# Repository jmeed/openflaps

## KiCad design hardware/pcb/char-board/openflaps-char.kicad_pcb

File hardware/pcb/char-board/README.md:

# Character Board (v0.1 draft)

One board per character, a drop-in replacement for the dowjames v5.1 module board in
[DrewFerg11/Split-Flap-Display](https://github.com/DrewFerg11/Split-Flap-Display). It
keeps Drew's outline and puts PREV, NEXT, MOTOR and HALL exactly where his board has
them (copied from his Edge_Cuts gerber and drill file), so it sits in his enclosure and
plugs into its neighbours the same way. It replaces I2C with the OpenFlaps UART ring:
no DIP switches, no address limit, addresses come from position in the chain.

Status: schematic drafted, outline and placement done, **not routed, not ERC/DRC
checked**. Not ordered.

| File | What |
|---|---|
| `gen_schematic.py` | Generates the schematic and symbol library |
| `gen_pcb.py` | Generates the board: Drew's outline, footprints placed, pads netted, no tracks |
| `openflaps-char.kicad_sch` / `.kicad_pcb` / `.kicad_pro` | KiCad project (opens in KiCad 7 or newer) |
| `Schematic_Character_Board.pdf`, `placement.png` | Renders |

Rebuild:

```bash
python3 gen_schematic.py
kicad-cli sch export pdf -o Schematic_Character_Board.pdf openflaps-char.kicad_sch
kicad-cli sch export netlist --format kicadxml -o openflaps-char.xml openflaps-char.kicad_sch
python3 gen_pcb.py   # needs KiCad's pcbnew Python module
```

Once routing starts by hand in KiCad, the `.kicad_pcb` becomes the source of truth and
`gen_pcb.py` should not be re-run over it.

## Circuit

- **MCU** PY32F002AF15P6 (TSSOP-20, LCSC C5292059) at 3.3 V from an XC6206P332MR LDO.
- **Motor**: ULN2003A, inputs PA6, PA5, PF0, PF1, outputs to a horizontal JST XH 5-pin
  (S5B-XH-A, C263757, as Drew), pin 5 = +5 V (red wire). COM to +5 V.
- **Hall sensor** (homing): JST PH 3-pin (C2320, as Drew), pinout `OUT GND +5V` in Drew's
  order so his A3144/WSH130 leads plug in. The sensor runs on 5 V; its open-collector
  output is pulled up to 3.3 V with 10k, so the MCU never sees 5 V. Active low on PB0,
  100 nF filter.
- **Ring link**: Drew's right-angle 1x4 PREV header (C32713263) and NEXT socket
  (C2897386), same positions and same pins 1-2 (GND, +5V). Pins 3-4 change from I2C to
  DATA and RETURN. Data enters at PREV (PA3, USART1 RX via 100 ohm) and leaves at NEXT
  (PA2, TX via 100 ohm). RETURN is a straight trace. Bridge **JP1** on the last board of a
  row to loop DATA back on RETURN.
- **Debug light**: one WS2812B-2020-V6 on 5 V, data from PA7 via 33 ohm (SPI1 MOSI if
  the AF table allows, otherwise bit-banged: one LED is about 30 us). Dim green power LED.
- **Flashing**: SWDIO, SWCLK, NRST, BOOT0, 3.3 V and GND on 1.5 mm pogo pads on the
  bottom, in a 2.54 mm row. BOOT0 has a 10k pull-down.
- **Spare I/O** on 1 mm bottom pads: PA0, PA1, PA4, PB1, PB2, PB3.

## MCU pin map

| Pin | Port | Net |
|---|---|---|
| 6, 7, 8, 9 | PA6, PA5, PF0, PF1 | Motor coils 1-4 (PF0/PF1 free because the internal oscillator is used) |
| 17 | PB0 | Hall sensor, active low |
| 14, 13 | PA3, PA2 | USART1 RX, TX (AF1) |
| 16 | PA7 | WS2812 data |
| 2, 3, 10, 5 | PA13, PA14, PF2, PF4 | SWDIO, SWCLK, NRST, BOOT0 |
| 11, 12, 15, 19, 18, 4 | PA0, PA1, PA4, PB1, PB2, PB3 | Spare pads |
| 20, 1 | VCC, VSS | 3.3 V, GND |

## Not yet checked

- Routing, then ERC and DRC in KiCad 8 or 9.
- PA7 as SPI1 MOSI on the PY32F002A (AF table); PA2/PA3 as USART1 AF1.
- Drew's board has no mounting holes; this one copies that. Check how it is held in the
  enclosure (and the narrower dual-display enclosure from MakerWorld) on a real build.
- LCSC numbers still to pick: 22 uF 1206 bulk cap, 3.3k, 33 ohm, green 0603 LED.
- One power pin per side on the 4-pin link: fine for one motor per board (Drew does the
  same), but inject 5 V every few modules on a long row.

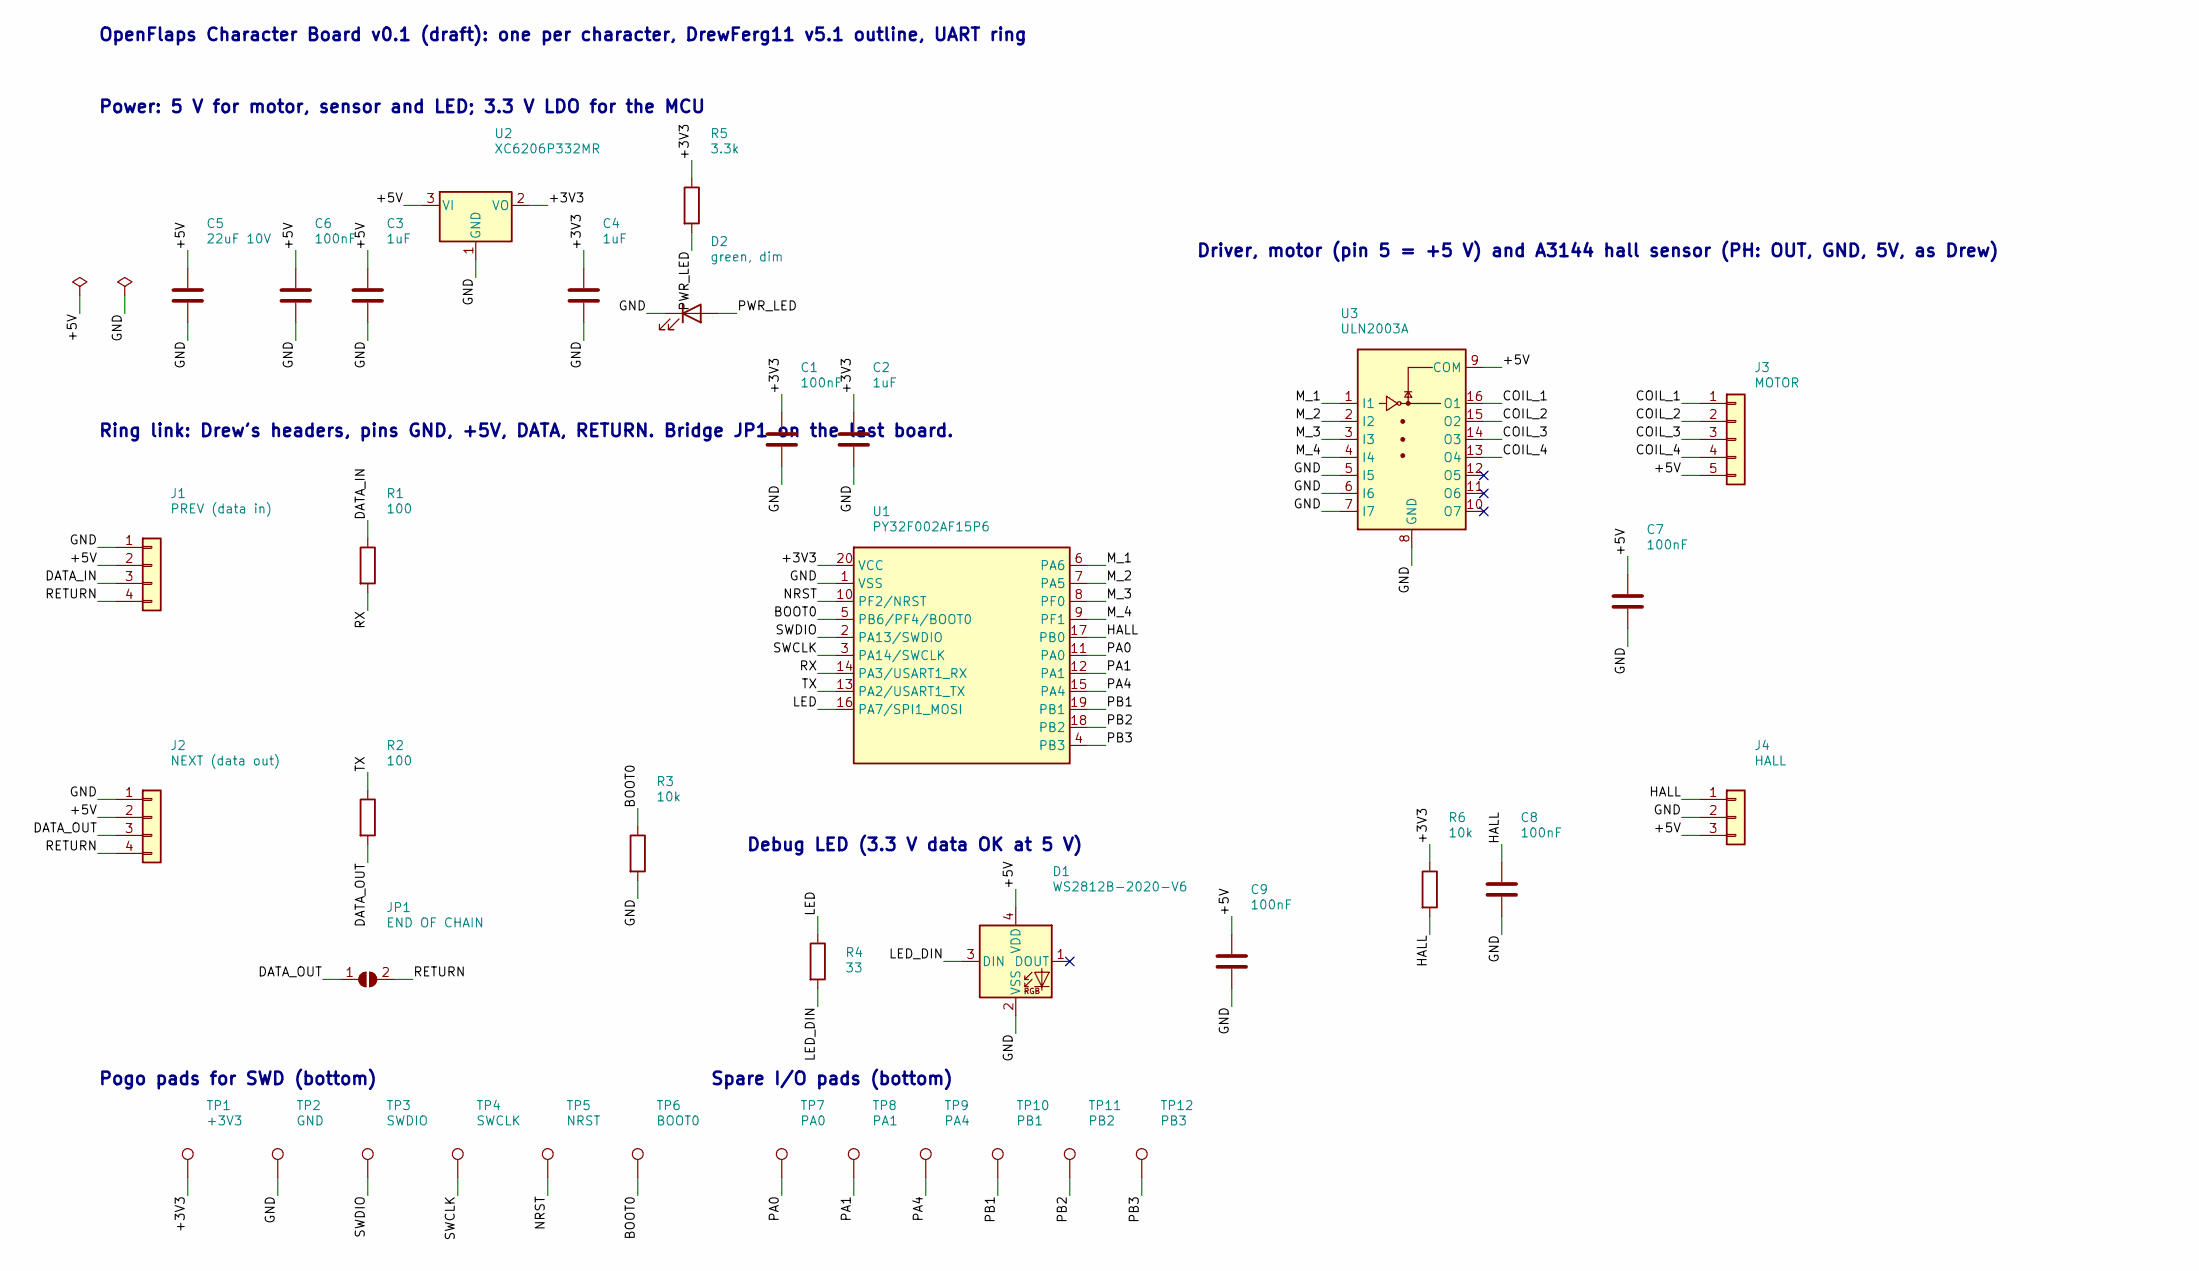
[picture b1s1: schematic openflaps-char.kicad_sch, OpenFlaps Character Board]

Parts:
C1, C6, C7, C8, C9: 100nF; C_0603_1608Metric; LCSC C14663
C2, C3, C4: 1uF; C_0603_1608Metric; LCSC C15849
C5: 22uF 10V; C_1206_3216Metric
D1: WS2812B-2020-V6; LED_WS2812B-2020_PLCC4_2.0x2.0mm; LCSC C52917434
D2: green, dim; LED_0603_1608Metric
J1: PREV (data in); PinHeader_1x04_P2.54mm_Horizontal; LCSC C32713263
J2: NEXT (data out); PinSocket_1x04_P2.54mm_Horizontal; LCSC C2897386
J3: MOTOR; JST_XH_S5B-XH-A_1x05_P2.50mm_Horizontal; LCSC C263757
J4: HALL; JST_PH_B3B-PH-K_1x03_P2.00mm_Vertical; LCSC C2320
JP1: END OF CHAIN; SolderJumper-2_P1.3mm_Open_RoundedPad1.0x1.5mm
R1, R2: 100; R_0603_1608Metric; LCSC C22775
R3, R6: 10k; R_0603_1608Metric; LCSC C25804
R4: 33; R_0603_1608Metric
R5: 3.3k; R_0603_1608Metric
TP1: +3V3; TestPoint_Pad_D1.5mm
TP2: GND; TestPoint_Pad_D1.5mm
TP3: SWDIO; TestPoint_Pad_D1.5mm
TP4: SWCLK; TestPoint_Pad_D1.5mm
TP5: NRST; TestPoint_Pad_D1.5mm
TP6: BOOT0; TestPoint_Pad_D1.5mm
TP7: PA0; TestPoint_Pad_D1.0mm
TP8: PA1; TestPoint_Pad_D1.0mm
TP9: PA4; TestPoint_Pad_D1.0mm
TP10: PB1; TestPoint_Pad_D1.0mm
TP11: PB2; TestPoint_Pad_D1.0mm
TP12: PB3; TestPoint_Pad_D1.0mm
U1: PY32F002AF15P6; TSSOP-20_4.4x6.5mm_P0.65mm; LCSC C5292059
U2: XC6206P332MR; SOT-23; LCSC C5446
U3: ULN2003A; SOIC-16_3.9x9.9mm_P1.27mm; LCSC C5252903

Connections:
+3V3: C1.1, C2.1, C4.1, R5.1, R6.1, TP1.1, U1.20 (VCC), U2.2 (VO)
+5V: C3.1, C5.1, C6.1, C7.1, C9.1, D1.4 (VDD), J1.2, J2.2, J3.5, J4.3, U2.3 (VI), U3.9 (COM)
BOOT0: R3.1, TP6.1, U1.5 (PB6/PF4/BOOT0)
COIL_1: J3.1, U3.16 (O1)
COIL_2: J3.2, U3.15 (O2)
COIL_3: J3.3, U3.14 (O3)
COIL_4: J3.4, U3.13 (O4)
DATA_IN: J1.3, R1.1
DATA_OUT: J2.3, JP1.1 (A), R2.2
GND: C1.2, C2.2, C3.2, C4.2, C5.2, C6.2, C7.2, C8.2, C9.2, D1.2 (VSS), D2.1 (K), J1.1, J2.1, J4.2, R3.2, TP2.1, U1.1 (VSS), U2.1 (GND), U3.5 (I5), U3.6 (I6), U3.7 (I7), U3.8 (GND)
HALL: C8.1, J4.1, R6.2, U1.17 (PB0)
LED: R4.1, U1.16 (PA7/SPI1_MOSI)
LED_DIN: D1.3 (DIN), R4.2
M_1: U1.6 (PA6), U3.1 (I1)
M_2: U1.7 (PA5), U3.2 (I2)
M_3: U1.8 (PF0), U3.3 (I3)
M_4: U1.9 (PF1), U3.4 (I4)
NRST: TP5.1, U1.10 (PF2/NRST)
PA0: TP7.1, U1.11 (PA0)
PA1: TP8.1, U1.12 (PA1)
PA4: TP9.1, U1.15 (PA4)
PB1: TP10.1, U1.19 (PB1)
PB2: TP11.1, U1.18 (PB2)
PB3: TP12.1, U1.4 (PB3)
PWR_LED: D2.2 (A), R5.2
RETURN: J1.4, J2.4, JP1.2 (B)
RX: R1.2, U1.14 (PA3/USART1_RX)
SWCLK: TP4.1, U1.3 (PA14/SWCLK)
SWDIO: TP3.1, U1.2 (PA13/SWDIO)
TX: R2.1, U1.13 (PA2/USART1_TX)

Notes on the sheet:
OpenFlaps Character Board v0.1 (draft): one per character, DrewFerg11 v5.1 outline, UART ring
Power: 5 V for motor, sensor and LED; 3.3 V LDO for the MCU
Ring link: Drew's headers, pins GND, +5V, DATA, RETURN. Bridge JP1 on the last board.
Driver, motor (pin 5 = +5 V) and A3144 hall sensor (PH: OUT, GND, 5V, as Drew)
Debug LED (3.3 V data OK at 5 V)
Pogo pads for SWD (bottom)
Spare I/O pads (bottom)

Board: 2 copper layers, 37 parts (12 on the bottom side), 30 nets, no tracks yet.

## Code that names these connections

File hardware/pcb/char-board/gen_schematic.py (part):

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MCU_LEFT = [  # (number, name, type)
    ("20", "VCC", "power_in"),
    ("1", "VSS", "power_in"),
    ("10", "PF2/NRST", "bidirectional"),
    ("5", "PB6/PF4/BOOT0", "input"),
    ("2", "PA13/SWDIO", "bidirectional"),
    ("3", "PA14/SWCLK", "bidirectional"),
    ("14", "PA3/USART1_RX", "bidirectional"),
    ("13", "PA2/USART1_TX", "bidirectional"),
    ("16", "PA7/SPI1_MOSI", "bidirectional"),
]
MCU_RIGHT = [(n, nm, "bidirectional") for n, nm in [
    ("6", "PA6"), ("7", "PA5"), ("8", "PF0"), ("9", "PF1"),
    ("17", "PB0"), ("11", "PA0"), ("12", "PA1"), ("15", "PA4"),
    ("19", "PB1"), ("18", "PB2"), ("4", "PB3"),
]]


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
# Drew's v5.1 board: PREV is a right-angle 1x4 pin header, NEXT a right-angle 1x4
# socket, both pinned GND, +5V, bus, bus. We keep his pinout and positions and
# turn the two bus pins into DATA and RETURN. Data enters at PREV.
mcu_nets = {
    "20": "+3V3", "1": "GND",
    "10": "NRST", "5": "BOOT0", "2": "SWDIO", "3": "SWCLK",
    "14": "RX", "13": "TX", "16": "LED",
    "6": "M_1", "7": "M_2", "8": "M_3", "9": "M_4",
    "17": "HALL",
    "11": "PA0", "12": "PA1", "15": "PA4", "19": "PB1", "18": "PB2", "4": "PB3",
}
part("U1", "openflaps:PY32F002A", "PY32F002AF15P6", "Package_SO:TSSOP-20_4.4x6.5mm_P0.65mm",
     "C5292059", (139.7, 106.68), mcu_nets, ref_at=(-12.7, -20.32))
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for k, net in enumerate(["+3V3", "GND", "SWDIO", "SWCLK", "NRST", "BOOT0"]):
    part(f"TP{k + 1}", "Connector:TestPoint", net, "TestPoint:TestPoint_Pad_D1.5mm", "",
         (30.48 + k * 12.7, 180.34), {"1": net})
for k, net in enumerate(["PA0", "PA1", "PA4", "PB1", "PB2", "PB3"]):
    part(f"TP{k + 7}", "Connector:TestPoint", net, "TestPoint:TestPoint_Pad_D1.0mm", "",
         (114.3 + k * 10.16, 180.34), {"1": net})
DNP = set()
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NOTES = [
    ((17.78, 20.32), "OpenFlaps Character Board v0.1 (draft): one per character, DrewFerg11 v5.1 outline, UART ring"),
    ((17.78, 30.48), "Power: 5 V for motor, sensor and LED; 3.3 V LDO for the MCU"),
    ((17.78, 76.2), "Ring link: Drew's headers, pins GND, +5V, DATA, RETURN. Bridge JP1 on the last board."),
    ((172.72, 50.8), "Driver, motor (pin 5 = +5 V) and A3144 hall sensor (PH: OUT, GND, 5V, as Drew)"),
    ((109.22, 134.62), "Debug LED (3.3 V data OK at 5 V)"),
    ((17.78, 167.64), "Pogo pads for SWD (bottom)"),
    ((104.14, 167.64), "Spare I/O pads (bottom)"),
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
